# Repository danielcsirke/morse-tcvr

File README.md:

# morse-tcvr
A BME-n a Nagyfrekvenciás Áramkörök Realizációja tárgyban készített morse adóvevő
KiCad version: 9.0

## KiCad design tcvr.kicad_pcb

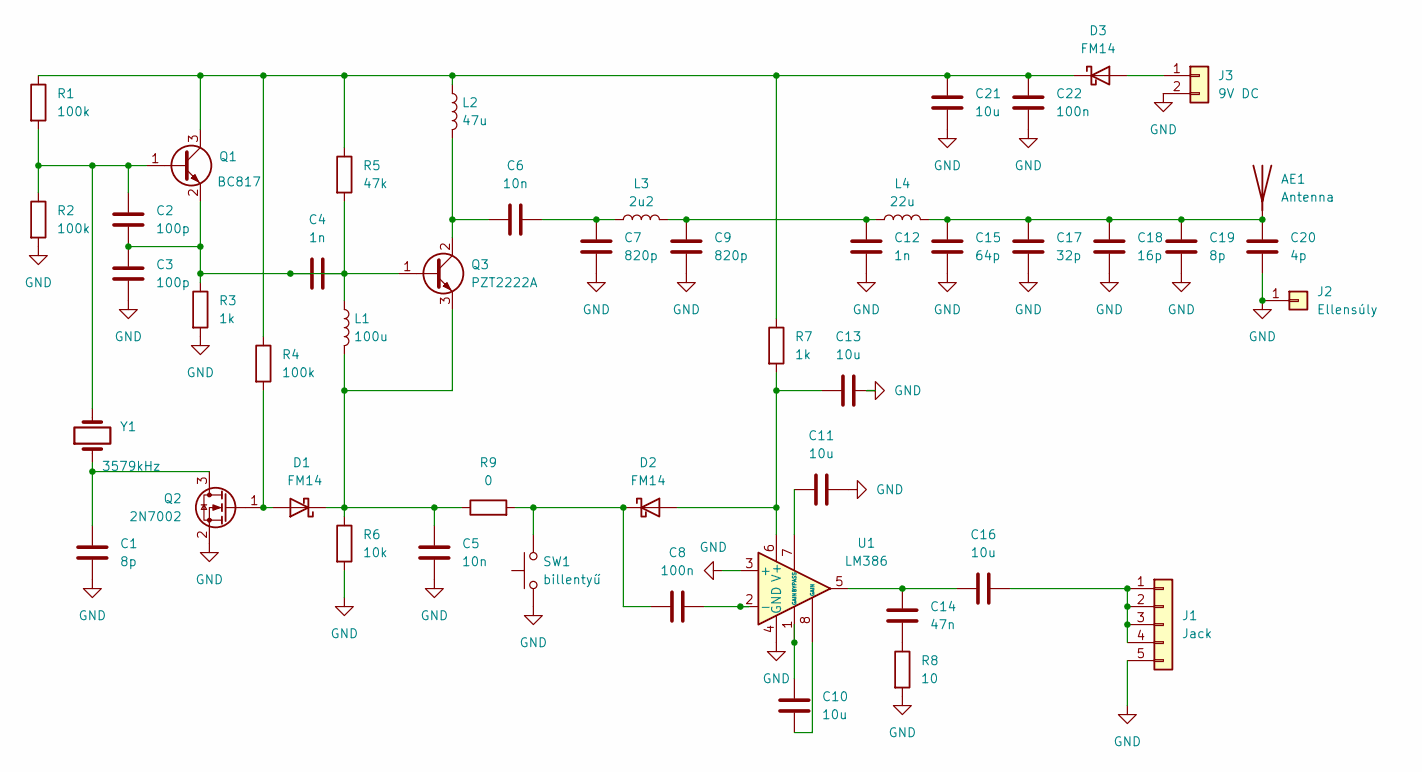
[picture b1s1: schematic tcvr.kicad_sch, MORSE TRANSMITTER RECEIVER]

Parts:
AE1: Antenna; TestPoint_Pad_3.0x3.0mm
C1, C19: 8p; C_0805_2012Metric
C2, C3: 100p; C_0805_2012Metric
C4, C12: 1n; C_0805_2012Metric
C5, C6: 10n; C_0805_2012Metric
C7, C9: 820p; C_0805_2012Metric
C8, C22: 100n; C_0805_2012Metric
C10, C11, C13, C16, C21: 10u; C_0805_2012Metric
C14: 47n; C_0805_2012Metric
C15: 64p; C_0805_2012Metric
C17: 32p; C_0805_2012Metric
C18: 16p; C_0805_2012Metric
C20: 4p; C_0805_2012Metric
D1, D2, D3: FM14; D_SOD-323_HandSoldering
J1: Jack; jack
J2: Ellensúly; TestPoint_Pad_3.0x3.0mm
J3: 9V DC; PinHeader_1x02_P2.54mm_Vertical
L1: 100u; L_1210_3225Metric
L2: 47u; L_Axial_L7.0mm_D3.3mm_P10.16mm_Horizontal_Fastron_MICC
L3: 2u2; L_Axial_L7.0mm_D3.3mm_P10.16mm_Horizontal_Fastron_MICC
L4: 22u; L_Axial_L7.0mm_D3.3mm_P10.16mm_Horizontal_Fastron_MICC
Q1: BC817; SOT-23
Q2: 2N7002; SOT-23
Q3: PZT2222A; SOT-223-3_TabPin2
R1, R2, R4: 100k; R_0805_2012Metric
R3, R7: 1k; R_0805_2012Metric
R5: 47k; R_0805_2012Metric
R6: 10k; R_0805_2012Metric
R8: 10; R_0805_2012Metric
R9: 0; R_1206_3216Metric
SW1: billentyű; bill
U1: LM386; SO-8_3.9x4.9mm_P1.27mm
Y1: 3579kHz; Crystal_SMD_HC49-SD

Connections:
GND: C1.2, C3.2, C5.2, C7.2, C9.2, C11.2, C12.2, C13.2, C15.2, C17.2, C18.2, C19.2, C20.2, C21.2, C22.2, J1.5, J2.1, J3.2, Q2.2 (S), R2.2, R3.2, R6.2, R8.2, SW1.1, U1.3 (+), U1.4 (GND)
unnamed: AE1.1 (A), C15.1, C17.1, C18.1, C19.1, C20.1, L4.2
unnamed: C6.2, C7.1, L3.1
unnamed: C10.1, U1.1 (GAIN)
unnamed: C10.2, U1.8 (GAIN)
unnamed: C9.1, C12.1, L3.2, L4.1
unnamed: C14.1, C16.1, U1.5
unnamed: C14.2, R8.1
unnamed: D1.2 (A), Q2.1 (G), R4.2
unnamed: C5.1, D1.1 (K), L1.2, Q3.3 (E), R6.1, R9.1
unnamed: C13.1, D2.2 (A), R7.2, U1.6 (V+)
unnamed: C8.1, D2.1 (K), R9.2, SW1.2
unnamed: D3.2 (A), J3.1
unnamed: C21.1, C22.1, D3.1 (K), L2.1, Q1.3 (C), R1.1, R4.1, R5.1, R7.1
unnamed: C16.2, J1.1, J1.2, J1.3, J1.4
unnamed: C2.1, Q1.1 (B), R1.2, R2.1, Y1.2
unnamed: C2.2, C3.1, C4.1, C4.2, L1.1, Q1.2 (E), Q3.1 (B), R3.1, R5.2
unnamed: C1.1, Q2.3 (D), Y1.1
unnamed: C6.1, L2.2, Q3.2 (C)
unnamed: C8.2, U1.2 (-)
unnamed: C11.1, U1.7 (BYPASS)

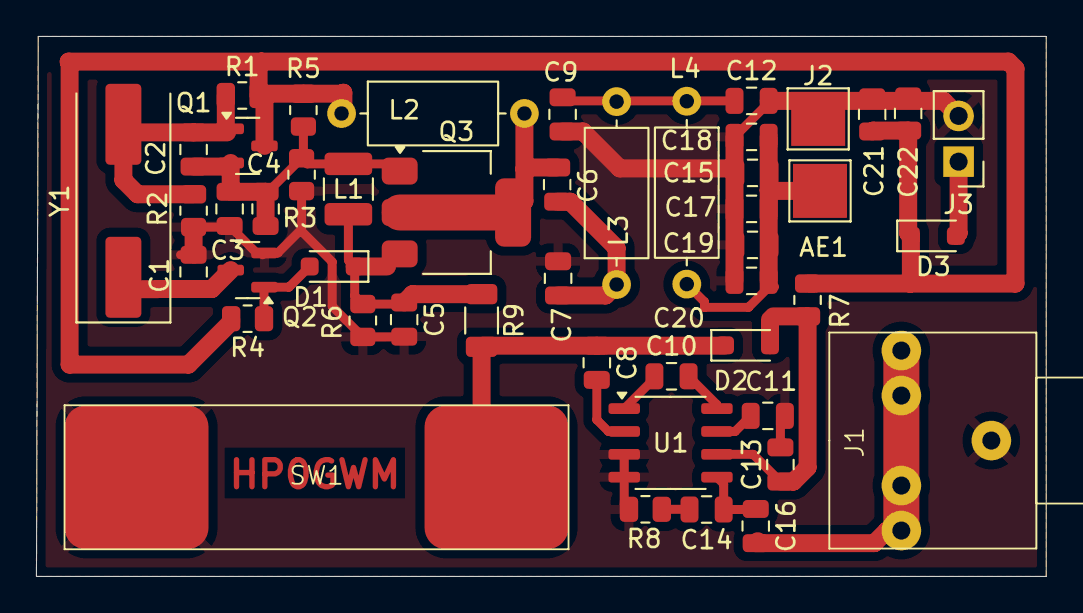
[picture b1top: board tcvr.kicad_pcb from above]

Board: 2 copper layers, 56.1 x 30.0 mm, 48 parts (0 on the bottom side), 21 nets.

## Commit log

2026-04-10 Add KiCad version to README
2026-04-15 added documentation latex document
2026-04-22 updated bom
2026-04-29 átkötött kondi javítva a kapcsrajzban, layouton még hibás
2026-05-20 final_version
